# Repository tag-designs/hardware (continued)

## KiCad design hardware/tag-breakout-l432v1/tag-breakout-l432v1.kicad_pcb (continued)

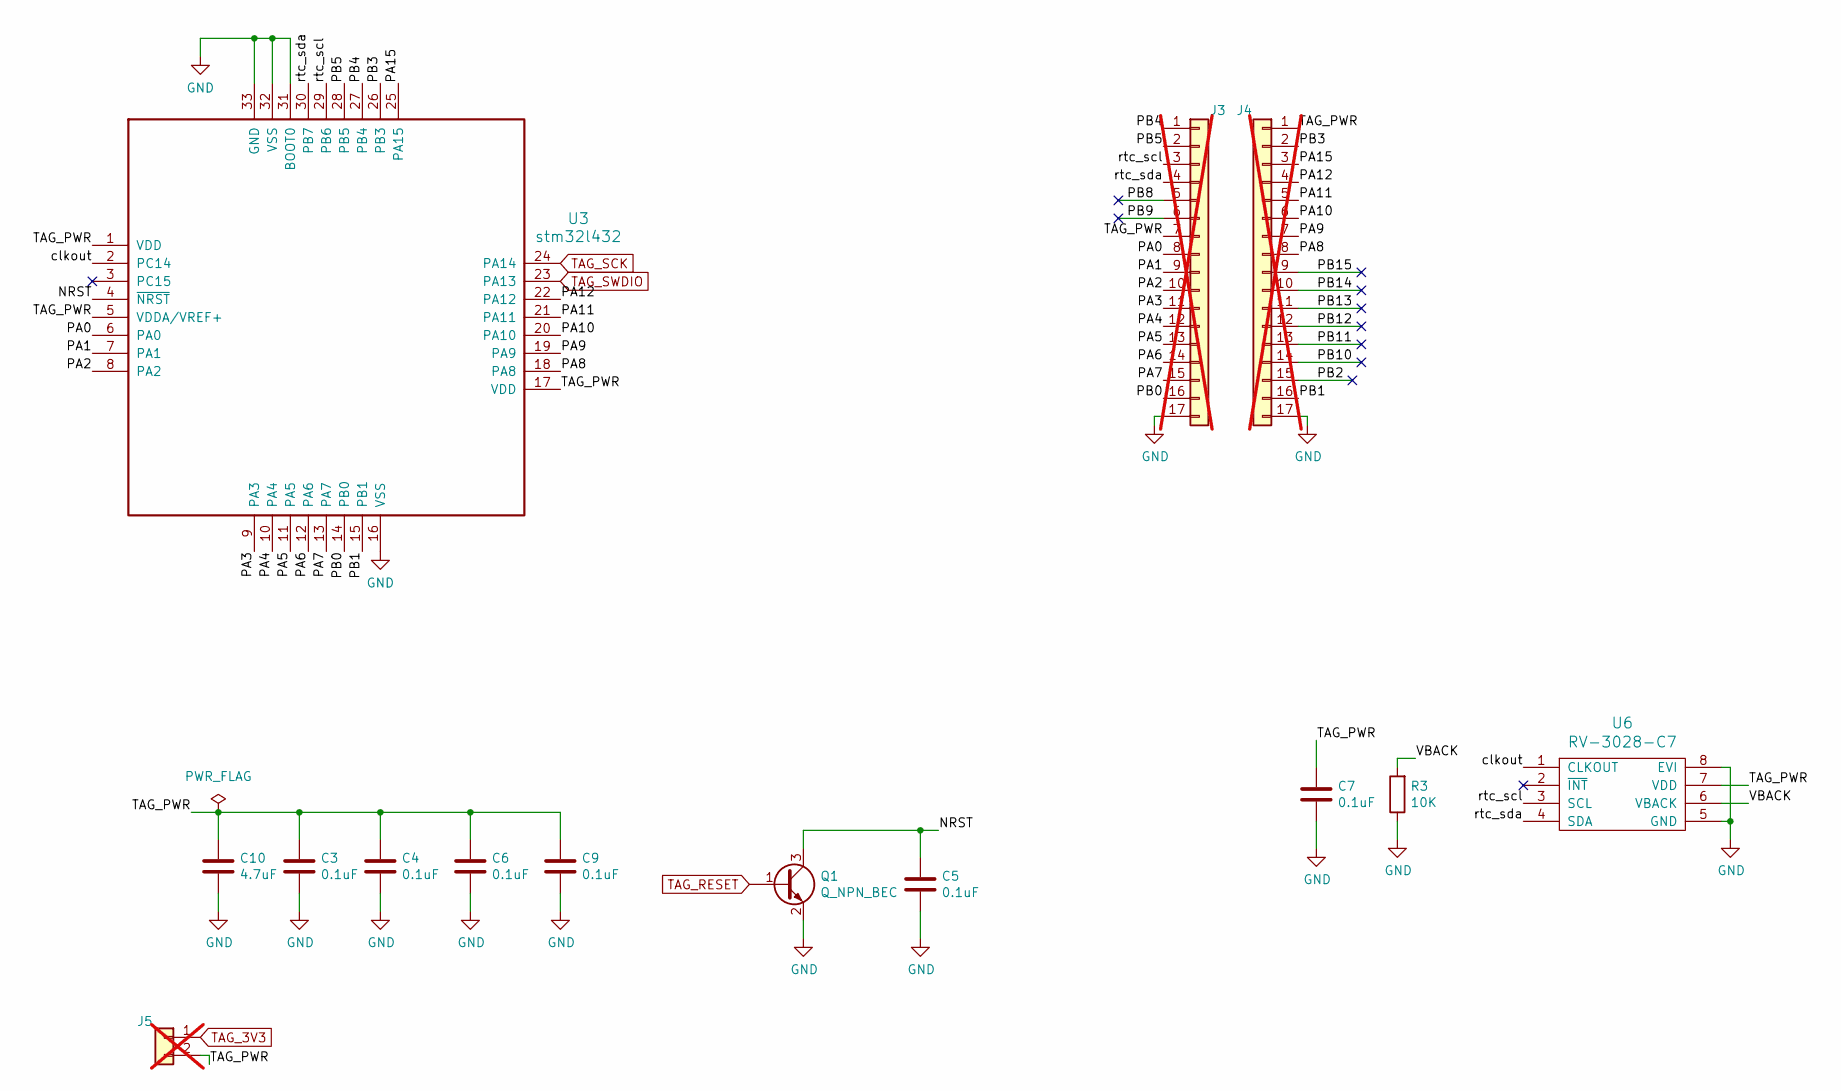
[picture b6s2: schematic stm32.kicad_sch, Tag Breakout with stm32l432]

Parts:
C3, C4, C5, C6, C7, C9: 0.1uF; C_0603_1608Metric; MPN CC0603KRX7R9BB104; LCSC C14663
C10: 4.7uF; C_0603_1608Metric; LCSC C19666
J3, J4: Conn_01x17; PinHeader_1x17_P2.54mm_Vertical_Staggered; not fitted
J5: Conn_01x02_Male; PinHeader_1x02_P2.54mm_Vertical; not fitted
Q1: Q_NPN_BEC; SOT-23; LCSC C20527
R3: 10K; R_0603_1608Metric; MPN 0603WAF1002T5E; LCSC C25804
U3: stm32l432; UFQFPN-32-1EP_5x5mm_P0.5mm_EP3.5x3.5mm; LCSC C94784
U6: RV-3028-C7; RV-8803-C7; LCSC C3019759

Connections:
/stm32/NRST: C5.1, Q1.3 (C), U3.4 (~NRST)
/stm32/PA0: J3.8, U3.6 (PA0)
/stm32/PA1: J3.9, U3.7 (PA1)
/stm32/PA2: J3.10, U3.8 (PA2)
/stm32/PA3: J3.11, U3.9 (PA3)
/stm32/PA4: J3.12, U3.10 (PA4)
/stm32/PA5: J3.13, U3.11 (PA5)
/stm32/PA6: J3.14, U3.12 (PA6)
/stm32/PA7: J3.15, U3.13 (PA7)
/stm32/PA8: J4.8, U3.18 (PA8)
/stm32/PA9: J4.7, U3.19 (PA9)
/stm32/PA10: J4.6, U3.20 (PA10)
/stm32/PA11: J4.5, U3.21 (PA11)
/stm32/PA12: J4.4, U3.22 (PA12)
/stm32/PA15: J4.3, U3.25 (PA15)
/stm32/PB0: J3.16, U3.14 (PB0)
/stm32/PB1: J4.16, U3.15 (PB1)
/stm32/PB2: J4.15
/stm32/PB3: J4.2, U3.26 (PB3)
/stm32/PB4: J3.1, U3.27 (PB4)
/stm32/PB5: J3.2, U3.28 (PB5)
/stm32/PB8: J3.5
/stm32/PB9: J3.6
/stm32/PB10: J4.14
/stm32/PB11: J4.13
/stm32/PB12: J4.12
/stm32/PB13: J4.11
/stm32/PB14: J4.10
/stm32/PB15: J4.9
/stm32/VBACK: R3.2, U6.6 (VBACK)
/stm32/clkout: U3.2 (PC14), U6.1 (CLKOUT)
/stm32/rtc_scl: J3.3, U3.29 (PB6), U6.3 (SCL)
/stm32/rtc_sda: J3.4, U3.30 (PB7), U6.4 (SDA)
GND: C3.2, C4.2, C5.2, C6.2, C7.2, C9.2, C10.2, J3.17, J4.17, Q1.2 (E), R3.1, U3.16 (VSS), U3.31 (BOOT0), U3.32 (VSS), U3.33 (GND), U6.5 (GND), U6.8 (EVI); also elsewhere on the board
TAG_3V3: C3.1, C4.1, C6.1, C7.1, C9.1, C10.1, J3.7, J4.1, J5.2, U3.1 (VDD), U3.5 (VDDA/VREF+), U3.17 (VDD), U6.7 (VDD); also elsewhere on the board
TAG_RESET: Q1.1 (B); also elsewhere on the board
TAG_SCK: U3.24 (PA14); also elsewhere on the board
TAG_SWDIO: U3.23 (PA13); also elsewhere on the board

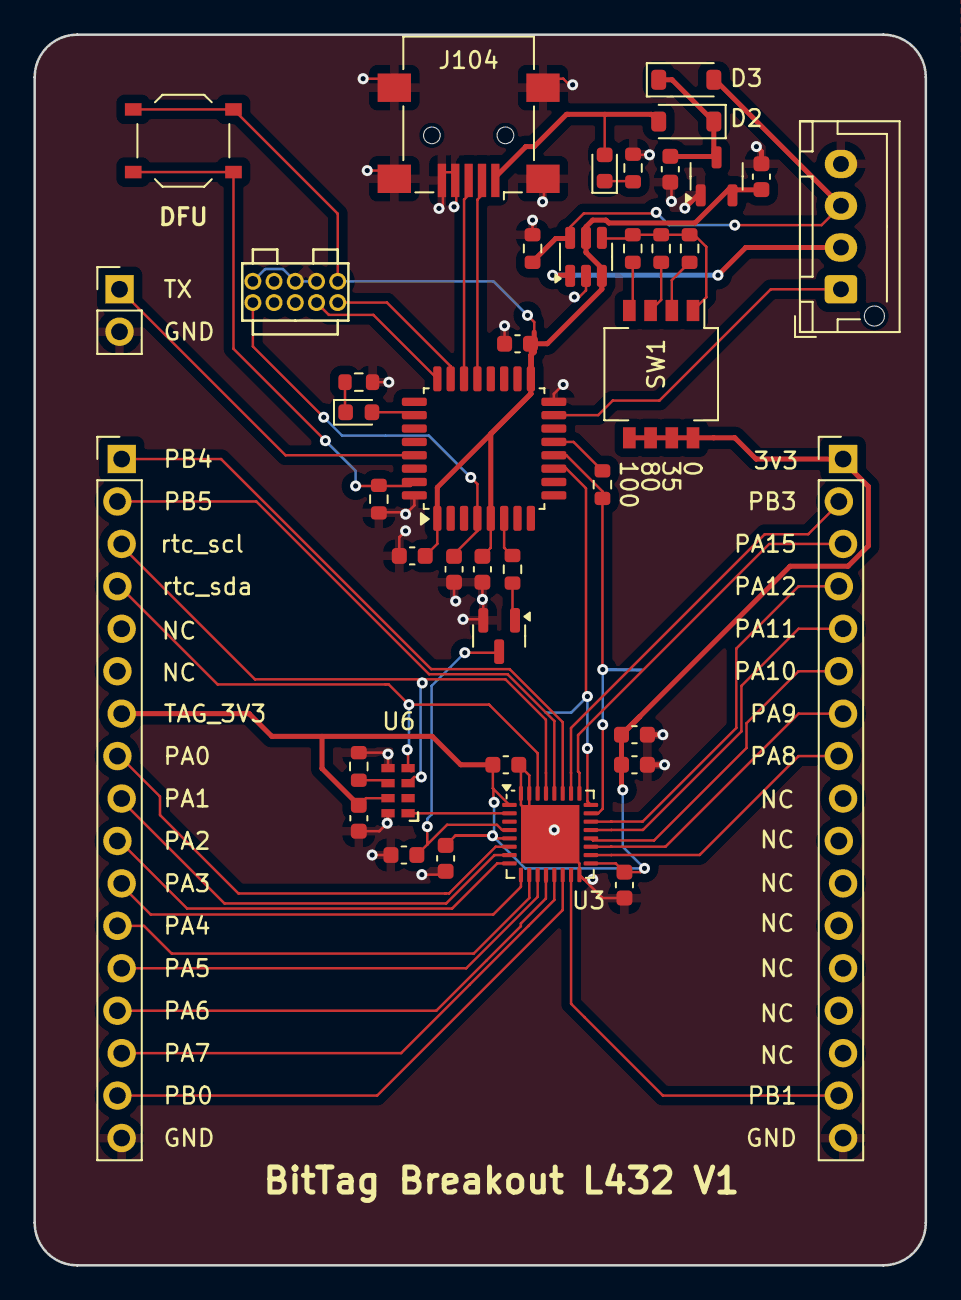
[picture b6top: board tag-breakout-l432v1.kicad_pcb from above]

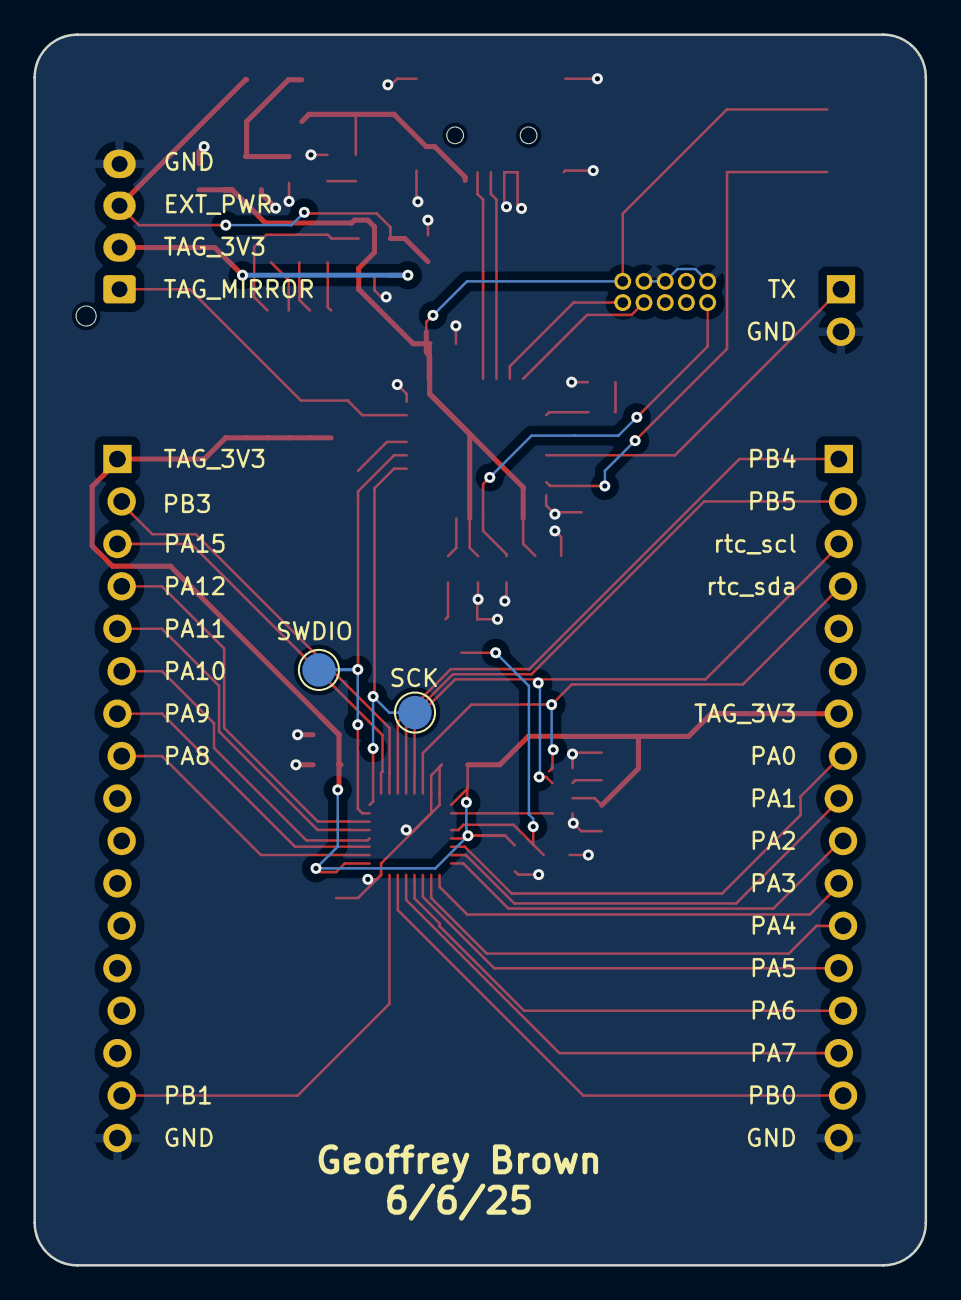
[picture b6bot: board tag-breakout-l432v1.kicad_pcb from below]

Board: 2 copper layers, 53.3 x 73.7 mm, 43 parts (2 on the bottom side), 51 nets.
